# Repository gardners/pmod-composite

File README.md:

PMOD Composite Output Board
===========================

Designed for use with FPGA boards used as DIY MEGA65 machines.

The DAC uses 4 FPGA pins per channel. It is designed for the
FPGA to massively over-sample the outputs to obtain 4 bits of
precision per FPGA line. Thus 16 bit precision per line should
be possible.  Most of the components on the board are the filter
to smooth out the switching noise from driving the pins at 540MHz
(270MHz DDR) to produce a nice clean 13.5MHz clocked composite
signal.  Should work fine as an audio DAC, too.

Design is all hole-through for easy assembly at home.

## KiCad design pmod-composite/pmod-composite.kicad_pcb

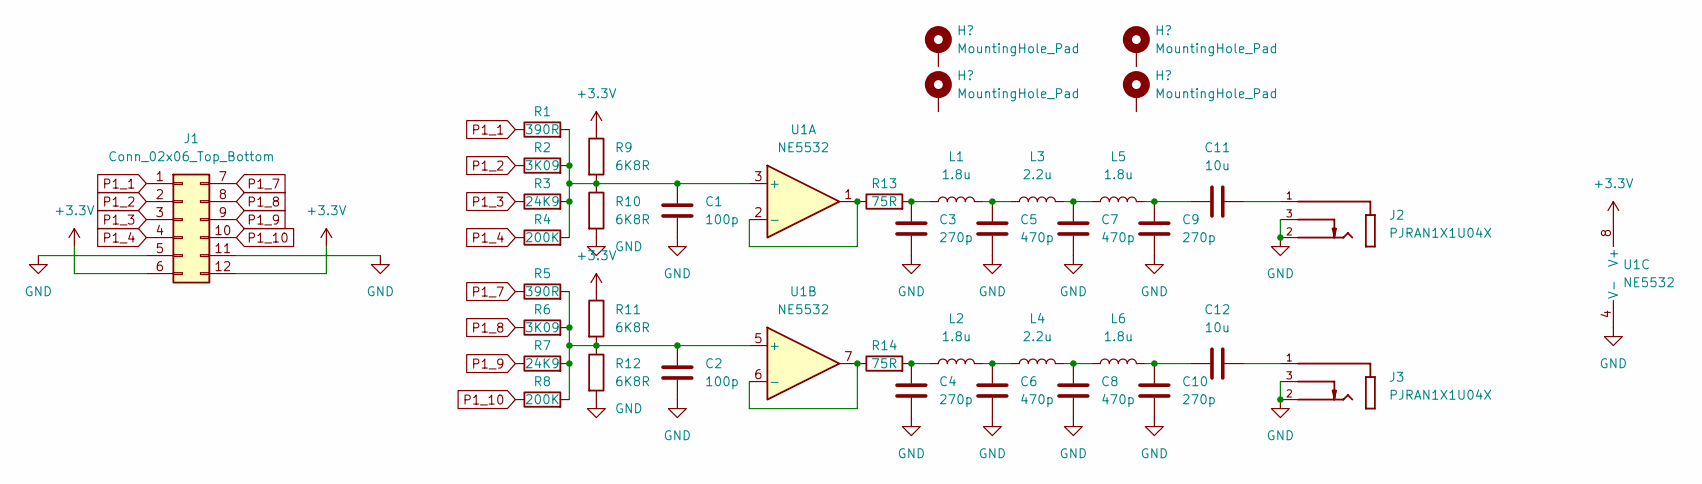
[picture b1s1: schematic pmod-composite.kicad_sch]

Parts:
C1, C2: 100p; C_Disc_D5.0mm_W2.5mm_P2.50mm
C3, C4, C9, C10: 270p; C_Disc_D5.0mm_W2.5mm_P2.50mm; DigikeyPart FG28C0G1H271JNT06
C5, C6, C7, C8: 470p; C_Disc_D5.0mm_W2.5mm_P2.50mm
C11, C12: 10u; C_Disc_D3.0mm_W2.0mm_P2.50mm; DigikeyPart FG18X5R1E106MRT06
J1: Conn_02x06_Top_Bottom; PMOD
J2, J3: PJRAN1X1U04X; SWITCHCRAFT_PJRAN1X1U04X; PARTREV A; DigikeyPart PJRAN1X1U04X-ND
L1, L2, L5, L6: 1.8u; L_Axial_L5.3mm_D2.2mm_P10.16mm_Horizontal_Vishay_IM-1; DigikeyPart 78F1R8K-RC
L3, L4: 2.2u; L_Axial_L5.3mm_D2.2mm_P10.16mm_Horizontal_Vishay_IM-1; DigikeyPart 78F2R2K-RC
R1, R5: 390R; R_Axial_DIN0207_L6.3mm_D2.5mm_P7.62mm_Horizontal
R2, R6: 3K09; R_Axial_DIN0207_L6.3mm_D2.5mm_P7.62mm_Horizontal
R3, R7: 24K9; R_Axial_DIN0207_L6.3mm_D2.5mm_P7.62mm_Horizontal
R4, R8: 200K; R_Axial_DIN0207_L6.3mm_D2.5mm_P7.62mm_Horizontal
R9, R10, R11, R12: 6K8R; R_Axial_DIN0207_L6.3mm_D2.5mm_P7.62mm_Horizontal
R13, R14: 75R; R_Axial_DIN0207_L6.3mm_D2.5mm_P7.62mm_Horizontal
U1: NE5532; DIP-8_W7.62mm

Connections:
+3V3: J1.6, J1.12, R9.1, R11.1, U1.8 (V+)
GND: C1.2, C2.2, C3.2, C4.2, C5.2, C6.2, C7.2, C8.2, C9.2, C10.2, J1.5, J1.11, J2.2, J2.3, J3.2, J3.3, R10.2, R12.2, U1.4 (V-)
unnamed: C1.1, R1.2, R2.2, R3.2, R4.2, R9.2, R10.1, U1.3 (+)
unnamed: C2.1, R5.2, R6.2, R7.2, R8.2, R11.2, R12.1, U1.5 (+)
unnamed: C3.1, L1.1, R13.2
unnamed: C4.1, L2.1, R14.2
unnamed: C5.1, L1.2, L3.1
unnamed: C6.1, L2.2, L4.1
unnamed: C7.1, L3.2, L5.1
unnamed: C8.1, L4.2, L6.1
unnamed: C10.1, C12.1, L6.2
unnamed: C9.1, C11.1, L5.2
unnamed: C11.2, J2.1
unnamed: C12.2, J3.1
unnamed: R13.1, U1.1, U1.2 (-)
unnamed: R14.1, U1.6 (-), U1.7
P1_1: J1.1, R1.1
P1_2: J1.2, R2.1
P1_3: J1.3, R3.1
P1_4: J1.4, R4.1
P1_7: J1.7, R5.1
P1_8: J1.8, R6.1
P1_9: J1.9, R7.1
P1_10: J1.10, R8.1

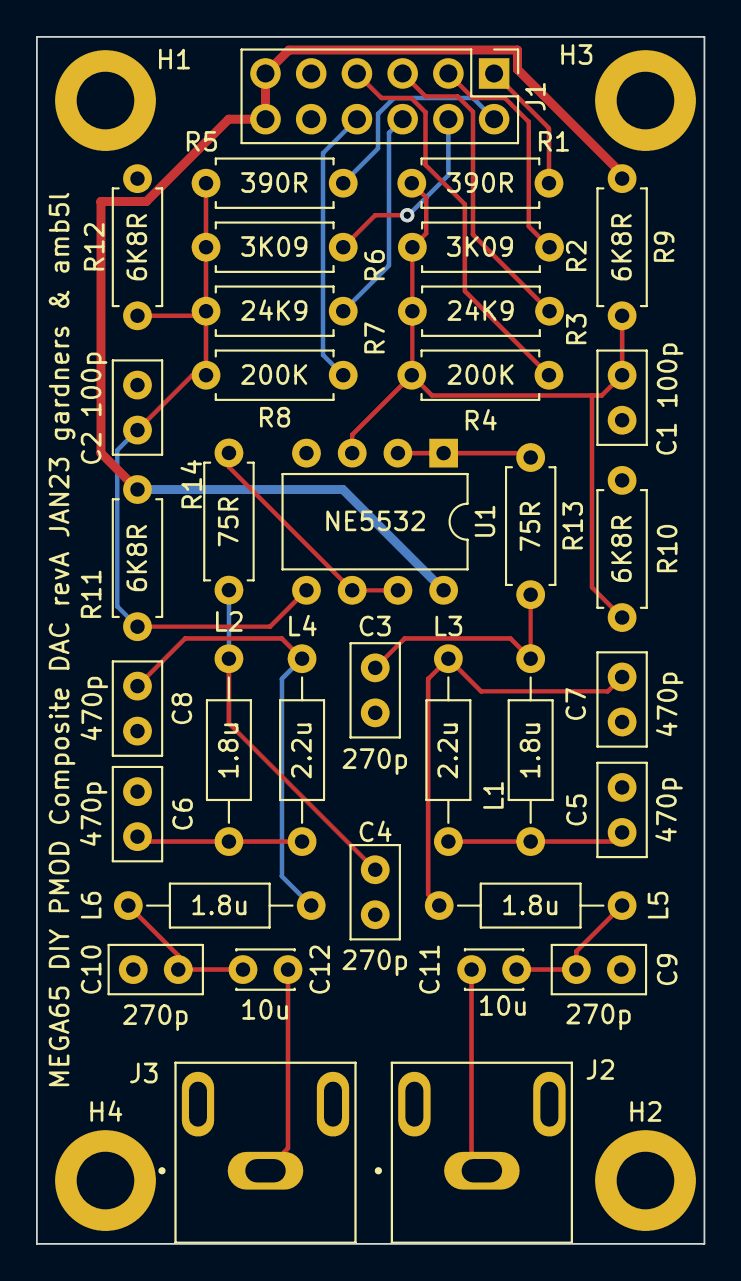
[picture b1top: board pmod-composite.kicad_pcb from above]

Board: 2 copper layers, 37.1 x 67.1 mm, 40 parts (0 on the bottom side), 24 nets.

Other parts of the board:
H1, H2, H3, H4: MountingHole_Pad; MountingHole_3.2mm_M3_DIN965_Pad

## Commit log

2023-01-04 begin implementing PMOD composite adaptor
2023-01-04 add many footprints
2023-01-04 add connector footprint
2023-01-04 work on PCB layout
2023-01-05 route board
2023-01-05 begin adding 3D models for components
2023-01-05 finish adding 3d models
2023-01-05 add README. Save remaining changes
2023-01-05 relocate README.
2023-01-05 add image to readme
